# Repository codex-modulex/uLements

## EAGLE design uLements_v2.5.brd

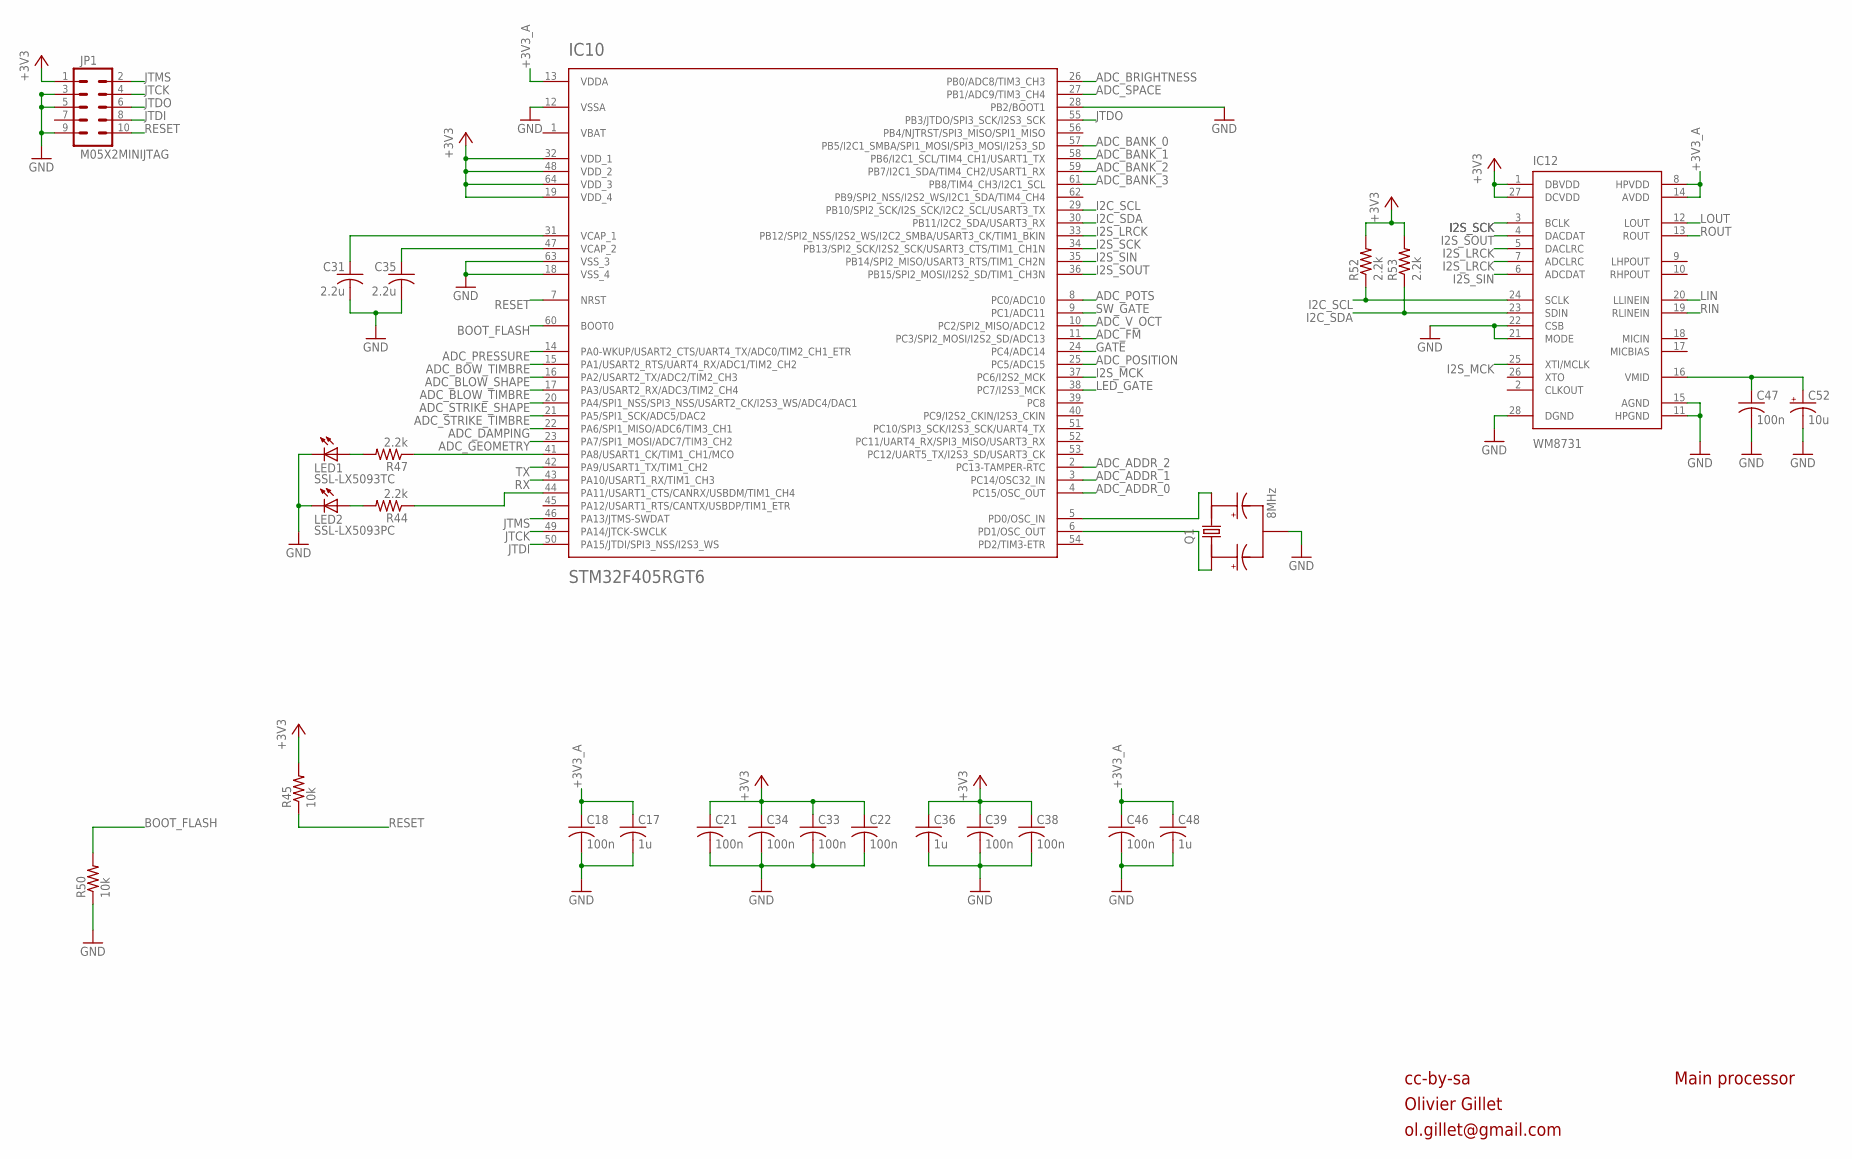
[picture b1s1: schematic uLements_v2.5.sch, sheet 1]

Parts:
C17, C36, C48: 1u; C0603
C18, C21, C22, C33, C34, C38, C39, C46, C47: 100n; C0603
C31, C35: 2.2u; C0805
C52: 10u; PANASONIC_B
IC10: STM32F405RGT6; TQFP-10X10-64
IC12: WM8731; SSOP28
JP1: M05X2MINIJTAG; 2X5-1.27
LED1: SSL-LX5093TC; LED5MM
LED2: SSL-LX5093PC; LED5MM
Q1: 8MHz; INSTRUO_CRYSTAL_SMALLER
R44, R47, R52, R53: 2.2k; R0603
R45, R50: 10k; R0603

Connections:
+3V3: C21.1, C22.1, C33.1, C34.1, C36.1, C38.1, C39.1, IC10.19 (VDD_4), IC10.32 (VDD_1), IC10.48 (VDD_2), IC10.64 (VDD_3), IC12.1 (DBVDD), IC12.27 (DCVDD), JP1.1, R45.2, R52.2, R53.2; also elsewhere on the board
+3V3_A: C17.1, C18.1, C46.1, C48.1, IC10.13 (VDDA), IC12.8 (HPVDD), IC12.14 (AVDD); also elsewhere on the board
ADC_ADDR_0: IC10.4 (PC15/OSC_OUT); also elsewhere on the board
ADC_ADDR_1: IC10.3 (PC14/OSC32_IN); also elsewhere on the board
ADC_ADDR_2: IC10.2 (PC13-TAMPER-RTC); also elsewhere on the board
ADC_BANK_0: IC10.57 (PB5/I2C1_SMBA/SPI1_MOSI/SPI3_MOSI/I2S3_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); also elsewhere on the board
ADC_BANK_1: IC10.58 (PB6/I2C1_SCL/TIM4_CH1/USART1_TX); also elsewhere on the board
ADC_BANK_2: IC10.59 (PB7/I2C1_SDA/TIM4_CH2/USART1_RX); also elsewhere on the board
ADC_BANK_3: IC10.61 (PB8/TIM4_CH3/I2C1_SCL); also elsewhere on the board
ADC_BLOW_SHAPE: IC10.16 (PA2/USART2_TX/ADC2/TIM2_CH3); also elsewhere on the board
ADC_BLOW_TIMBRE: IC10.17 (PA3/USART2_RX/ADC3/TIM2_CH4); also elsewhere on the board
ADC_BOW_TIMBRE: IC10.15 (PA1/USART2_RTS/UART4_RX/ADC1/TIM2_CH2); also elsewhere on the board
ADC_BRIGHTNESS: IC10.26 (PB0/ADC8/TIM3_CH3); also elsewhere on the board
ADC_DAMPING: IC10.22 (PA6/SPI1_MISO/ADC6/TIM3_CH1); also elsewhere on the board
ADC_FM: IC10.11 (PC3/SPI2_MOSI/I2S2_SD/ADC13); also elsewhere on the board
ADC_GEOMETRY: IC10.23 (PA7/SPI1_MOSI/ADC7/TIM3_CH2); also elsewhere on the board
ADC_POSITION: IC10.25 (PC5/ADC15); also elsewhere on the board
ADC_POTS: IC10.8 (PC0/ADC10); also elsewhere on the board
ADC_PRESSURE: IC10.14 (PA0-WKUP/USART2_CTS/UART4_TX/ADC0/TIM2_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); also elsewhere on the board
ADC_SPACE: IC10.27 (PB1/ADC9/TIM3_CH4); also elsewhere on the board
ADC_STRIKE_SHAPE: IC10.20 (PA4/SPI1_NSS/SPI3_NSS/USART2_CK/I2S3_WS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); also elsewhere on the board
ADC_STRIKE_TIMBRE: IC10.21 (PA5/SPI1_SCK/ADC5/DAC2); also elsewhere on the board
ADC_V_OCT: IC10.10 (PC2/SPI2_MISO/ADC12); also elsewhere on the board
BOOT_FLASH: IC10.60 (BOOT0), R50.2
GATE: IC10.24 (PC4/ADC14); also elsewhere on the board
GND: C17.2, C18.2, C21.2, C22.2, C31.2, C33.2, C34.2, C35.2, C36.2, C38.2, C39.2, C46.2, C47.2, C48.2, C52.-, IC10.12 (VSSA), IC10.18 (VSS_4), IC10.28 (PB2/BOOT1), IC10.63 (VSS_3), IC12.11 (HPGND), IC12.15 (AGND), IC12.21 (MODE), IC12.22 (CSB), IC12.28 (DGND), JP1.3, JP1.5, JP1.9, LED1.K (C), LED2.K (C), Q1.GND, R50.1; also elsewhere on the board
I2C_SCL: IC10.29 (PB10/SPI2_SCK/I2S_SCK/I2C2_SCL/USART3_TX), IC12.24 (SCLK), R52.1
I2C_SDA: IC10.30 (PB11/I2C2_SDA/USART3_RX), IC12.23 (SDIN), R53.1
I2S_LRCK: IC10.33 (PB12/SPI2_NSS/I2S2_WS/I2C2_SMBA/USART3_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), IC12.5 (DACLRC), IC12.7 (ADCLRC)
I2S_MCK: IC10.37 (PC6/I2S2_MCK), IC12.25 (XTI/MCLK)
I2S_SCK: IC10.34 (PB13/SPI2_SCK/I2S2_SCK/USART3_CTS/TIM1_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), IC12.3 (BCLK)
I2S_SIN: IC10.35 (PB14/SPI2_MISO/USART3_RTS/TIM1_CH2N), IC12.6 (ADCDAT)
I2S_SOUT: IC10.36 (PB15/SPI2_MOSI/I2S2_SD/TIM1_CH3N), IC12.4 (DACDAT)
JTCK: IC10.49 (PA14/JTCK-SWCLK), JP1.4
JTDI: IC10.50 (PA15/JTDI/SPI3_NSS/I2S3_WS), JP1.8
JTDO: IC10.55 (PB3/JTDO/SPI3_SCK/I2S3_SCK), JP1.6
JTMS: IC10.46 (PA13/JTMS-SWDAT), JP1.2
LED_GATE: IC10.38 (PC7/I2S3_MCK); also elsewhere on the board
LIN: IC12.20 (LLINEIN); also elsewhere on the board
LOUT: IC12.12 (LOUT); also elsewhere on the board
unnamed: IC10.5 (PD0/OSC_IN), Q1.X2
unnamed: IC10.6 (PD1/OSC_OUT), Q1.X1
unnamed: C35.1, IC10.47 (VCAP_2)
unnamed: C47.1, C52.+, IC12.16 (VMID)
unnamed: C31.1, IC10.31 (VCAP_1)
unnamed: IC10.44 (PA11/USART1_CTS/CANRX/USBDM/TIM1_CH4), R44.1
unnamed: LED2.A, R44.2
unnamed: LED1.A, R47.2
unnamed: IC10.41 (PA8/USART1_CK/TIM1_CH1/MCO), R47.1
RESET: IC10.7 (NRST), JP1.10, R45.1
RIN: IC12.19 (RLINEIN); also elsewhere on the board
ROUT: IC12.13 (ROUT); also elsewhere on the board
RX: IC10.43 (PA10/USART1_RX/TIM1_CH3)
SW_GATE: IC10.9 (PC1/ADC11); also elsewhere on the board
TX: IC10.42 (PA9/USART1_TX/TIM1_CH2)
VBAT: IC10.1 (VBAT)

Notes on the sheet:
cc-by-sa
Olivier Gillet
ol.gillet@gmail.com
Main processor

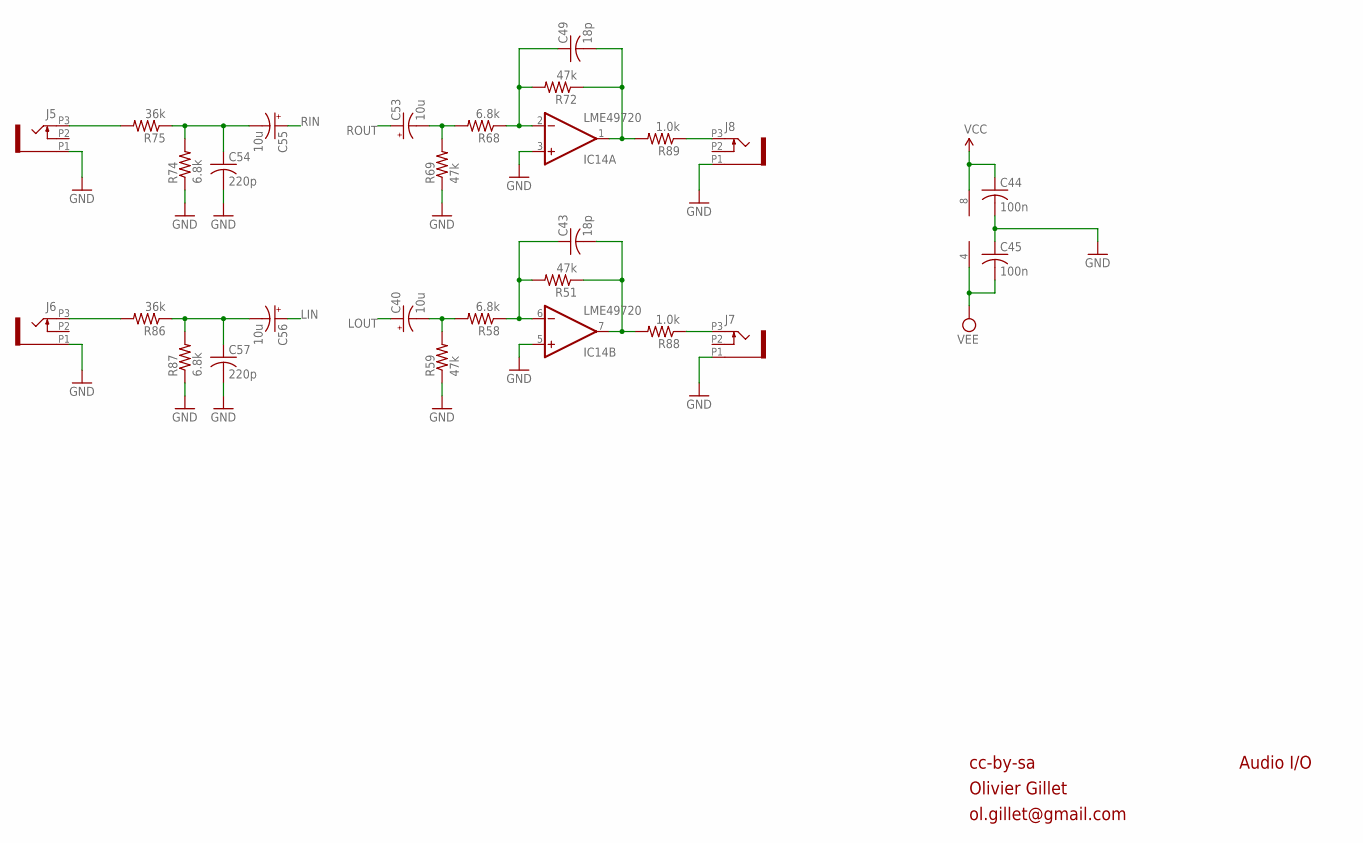
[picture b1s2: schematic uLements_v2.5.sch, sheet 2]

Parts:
C40, C53, C55, C56: 10u; PANASONIC_B
C43, C49: 18p; C0603
C44, C45: 100n; C0603
C54, C57: 220p; C0603
IC14: LME49720; SO08
J5, J6, J7, J8: PJ301_THONKICONN6; WQP_PJ_301M6
R51, R59, R69, R72: 47k; R0603
R58, R68, R74, R87: 6.8k; R0603
R75, R86: 36k; R0603
R88, R89: 1.0k; R0603

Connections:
GND: C44.2, C45.1, C54.2, C57.2, IC14.3 (+IN), IC14.5 (+IN), J5.P1 (1), J6.P1 (1), J7.P1 (1), J8.P1 (1), R59.1, R69.1, R74.1, R87.1; also elsewhere on the board
LIN: C56.+; also elsewhere on the board
LOUT: C40.+; also elsewhere on the board
LOUT_JACK: J8.P3 (3), R89.1
unnamed: C56.-, C57.1, R86.1, R87.2
unnamed: J5.P3 (3), R75.2
unnamed: J6.P3 (3), R86.2
unnamed: C54.1, C55.-, R74.2, R75.1
unnamed: C40.-, R58.2, R59.2
unnamed: C43.1, IC14.6 (-IN), R51.2, R58.1
unnamed: C43.2, IC14.7 (OUT), R51.1, R88.2
unnamed: C53.-, R68.2, R69.2
unnamed: C49.1, IC14.2 (-IN), R68.1, R72.2
unnamed: C49.2, IC14.1 (OUT), R72.1, R89.2
RIN: C55.+; also elsewhere on the board
ROUT: C53.+; also elsewhere on the board
ROUT_JACK: J7.P3 (3), R88.1
VCC: C44.1, IC14.8 (V+); also elsewhere on the board
VEE: C45.2, IC14.4 (V-); also elsewhere on the board

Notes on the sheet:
cc-by-sa
Olivier Gillet
ol.gillet@gmail.com
Audio I/O

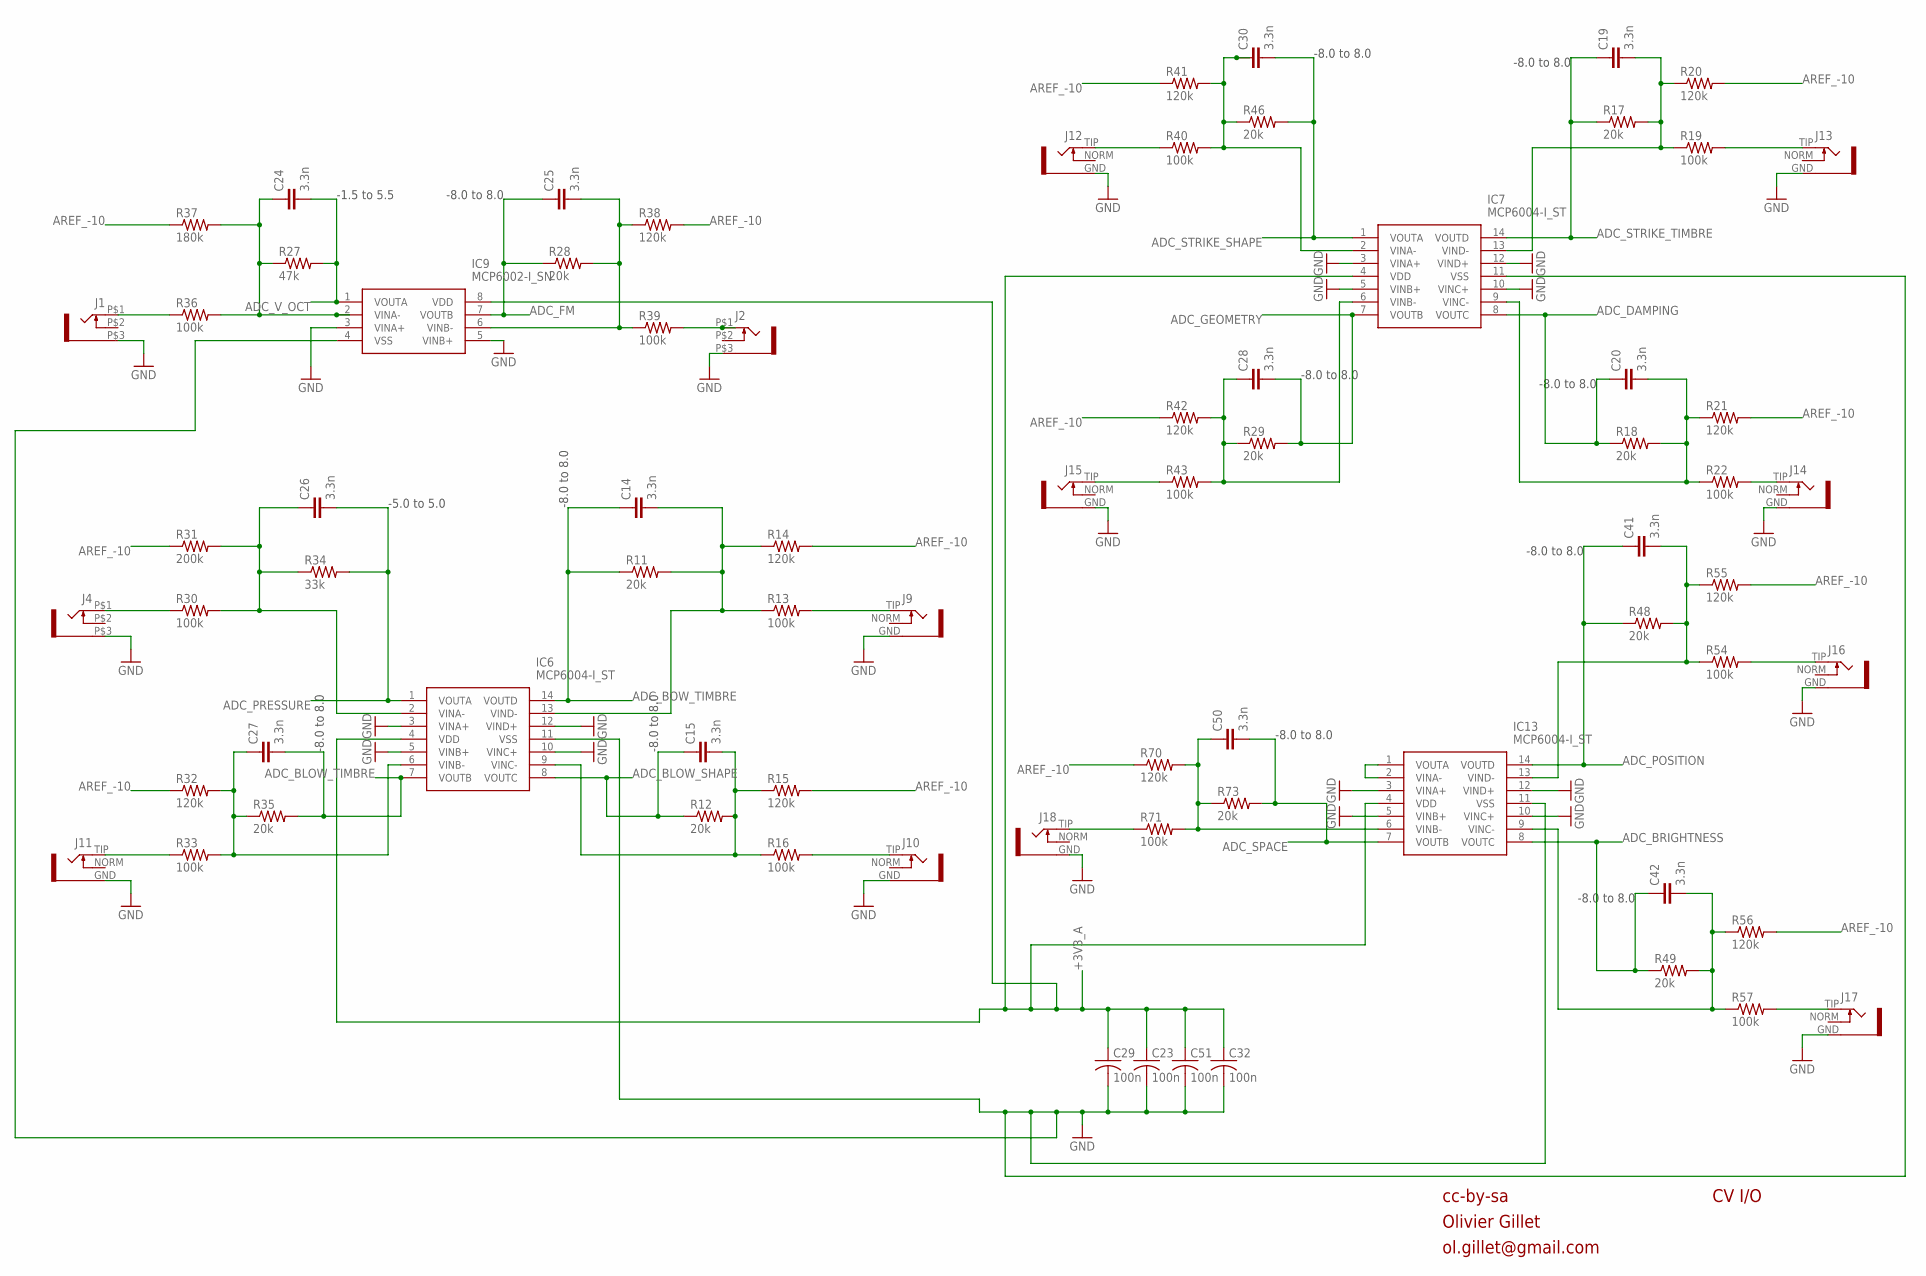
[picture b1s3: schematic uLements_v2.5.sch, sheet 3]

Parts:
C14, C15, C19, C20, C24, C25, C26, C27, C28, C30, C41, C42, C50: 3.3n; C0603
C23, C29, C32, C51: 100n; C0603
IC6, IC7, IC13: MCP6004-I_ST; SOP65P640X120-14N
IC9: MCP6002-I_SN; SOIC127P600X175-8N
J1, J2, J4: WQP-PJ301M-12_JACK
J9, J10, J11, J12, J13, J14, J15, J16, J17, J18: INSTRUO_S_JACK_S2_INV
R11, R12, R17, R18, R28, R29, R35, R46, R48, R49, R73: 20k; R0603
R13, R16, R19, R22, R30, R33, R36, R39, R40, R43, R54, R57, R71: 100k; R0603
R14, R15, R20, R21, R32, R38, R41, R42, R55, R56, R70: 120k; R0603
R27: 47k; R0603
R31: 200k; R0603
R34: 33k; R0603
R37: 180k; R0603

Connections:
+3V3_A: C23.1, C29.1, C32.1, C51.1, IC6.4 (VDD), IC7.4 (VDD), IC9.8 (VDD), IC13.4 (VDD); also elsewhere on the board
ADC_BLOW_SHAPE: C15.1, IC6.8 (VOUTC), R12.1; also elsewhere on the board
ADC_BLOW_TIMBRE: C27.2, IC6.7 (VOUTB), R35.2; also elsewhere on the board
ADC_BOW_TIMBRE: C14.1, IC6.14 (VOUTD), R11.1; also elsewhere on the board
ADC_BRIGHTNESS: C42.1, IC13.8 (VOUTC), R49.1; also elsewhere on the board
ADC_DAMPING: C20.1, IC7.8 (VOUTC), R18.1; also elsewhere on the board
ADC_FM: C25.1, IC9.7 (VOUTB), R28.1; also elsewhere on the board
ADC_GEOMETRY: C28.2, IC7.7 (VOUTB), R29.2; also elsewhere on the board
ADC_POSITION: C41.1, IC13.14 (VOUTD), R48.1; also elsewhere on the board
ADC_PRESSURE: C26.2, IC6.1 (VOUTA), R34.2; also elsewhere on the board
ADC_SPACE: C50.2, IC13.7 (VOUTB), R73.2; also elsewhere on the board
ADC_STRIKE_SHAPE: C30.2, IC7.1 (VOUTA), R46.2; also elsewhere on the board
ADC_STRIKE_TIMBRE: C19.1, IC7.14 (VOUTD), R17.1; also elsewhere on the board
ADC_V_OCT: C24.2, IC9.1 (VOUTA), R27.2; also elsewhere on the board
AREF_-10: R14.2, R15.2, R20.2, R21.2, R31.1, R32.1, R37.1, R38.2, R41.1, R42.1, R55.2, R56.2, R70.1; also elsewhere on the board
GND: C23.2, C29.2, C32.2, C51.2, IC6.3 (VINA+), IC6.5 (VINB+), IC6.10 (VINC+), IC6.11 (VSS), IC6.12 (VIND+), IC7.3 (VINA+), IC7.5 (VINB+), IC7.10 (VINC+), IC7.11 (VSS), IC7.12 (VIND+), IC9.3 (VINA+), IC9.4 (VSS), IC9.5 (VINB+), IC13.3 (VINA+), IC13.5 (VINB+), IC13.10 (VINC+), IC13.11 (VSS), IC13.12 (VIND+), J1.P$3 (1), J2.P$3 (1), J4.P$3 (1), J9.GND, J10.GND, J11.GND, J12.GND, J13.GND, J14.GND, J15.GND, J16.GND, J17.GND, J18.GND; also elsewhere on the board
unnamed: J15.TIP, R43.1
unnamed: C28.1, IC7.6 (VINB-), R29.1, R42.2, R43.2
unnamed: C20.2, IC7.9 (VINC-), R18.2, R21.1, R22.1
unnamed: J18.TIP, R71.1
unnamed: C41.2, IC13.13 (VIND-), R48.2, R54.1, R55.1
unnamed: J11.TIP, R33.1
unnamed: IC13.1 (VOUTA), IC13.2 (VINA-)
unnamed: J4.P$1 (2), R30.1
unnamed: J14.TIP, R22.2
unnamed: C50.1, IC13.6 (VINB-), R70.2, R71.2, R73.1
unnamed: C26.1, IC6.2 (VINA-), R30.2, R31.2, R34.1
unnamed: J13.TIP, R19.2
unnamed: J16.TIP, R54.2
unnamed: J17.TIP, R57.2
unnamed: C19.2, IC7.13 (VIND-), R17.2, R19.1, R20.1
unnamed: C42.2, IC13.9 (VINC-), R49.2, R56.1, R57.1
unnamed: J12.TIP, R40.1
unnamed: C25.2, IC9.6 (VINB-), R28.2, R38.1, R39.1
unnamed: C27.1, IC6.6 (VINB-), R32.2, R33.2, R35.1
unnamed: J10.TIP, R16.2
unnamed: C30.1, IC7.2 (VINA-), R40.2, R41.2, R46.1
unnamed: J1.P$1 (2), R36.1
unnamed: J2.P$1 (2), R39.2
unnamed: C24.1, IC9.2 (VINA-), R27.1, R36.2, R37.2
unnamed: J9.TIP, R13.2
unnamed: C15.2, IC6.9 (VINC-), R12.2, R15.1, R16.1
unnamed: C14.2, IC6.13 (VIND-), R11.2, R13.1, R14.1

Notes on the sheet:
cc-by-sa
Olivier Gillet
ol.gillet@gmail.com
CV I/O
-1.5 to 5.5
-8.0 to 8.0
-5.0 to 5.0

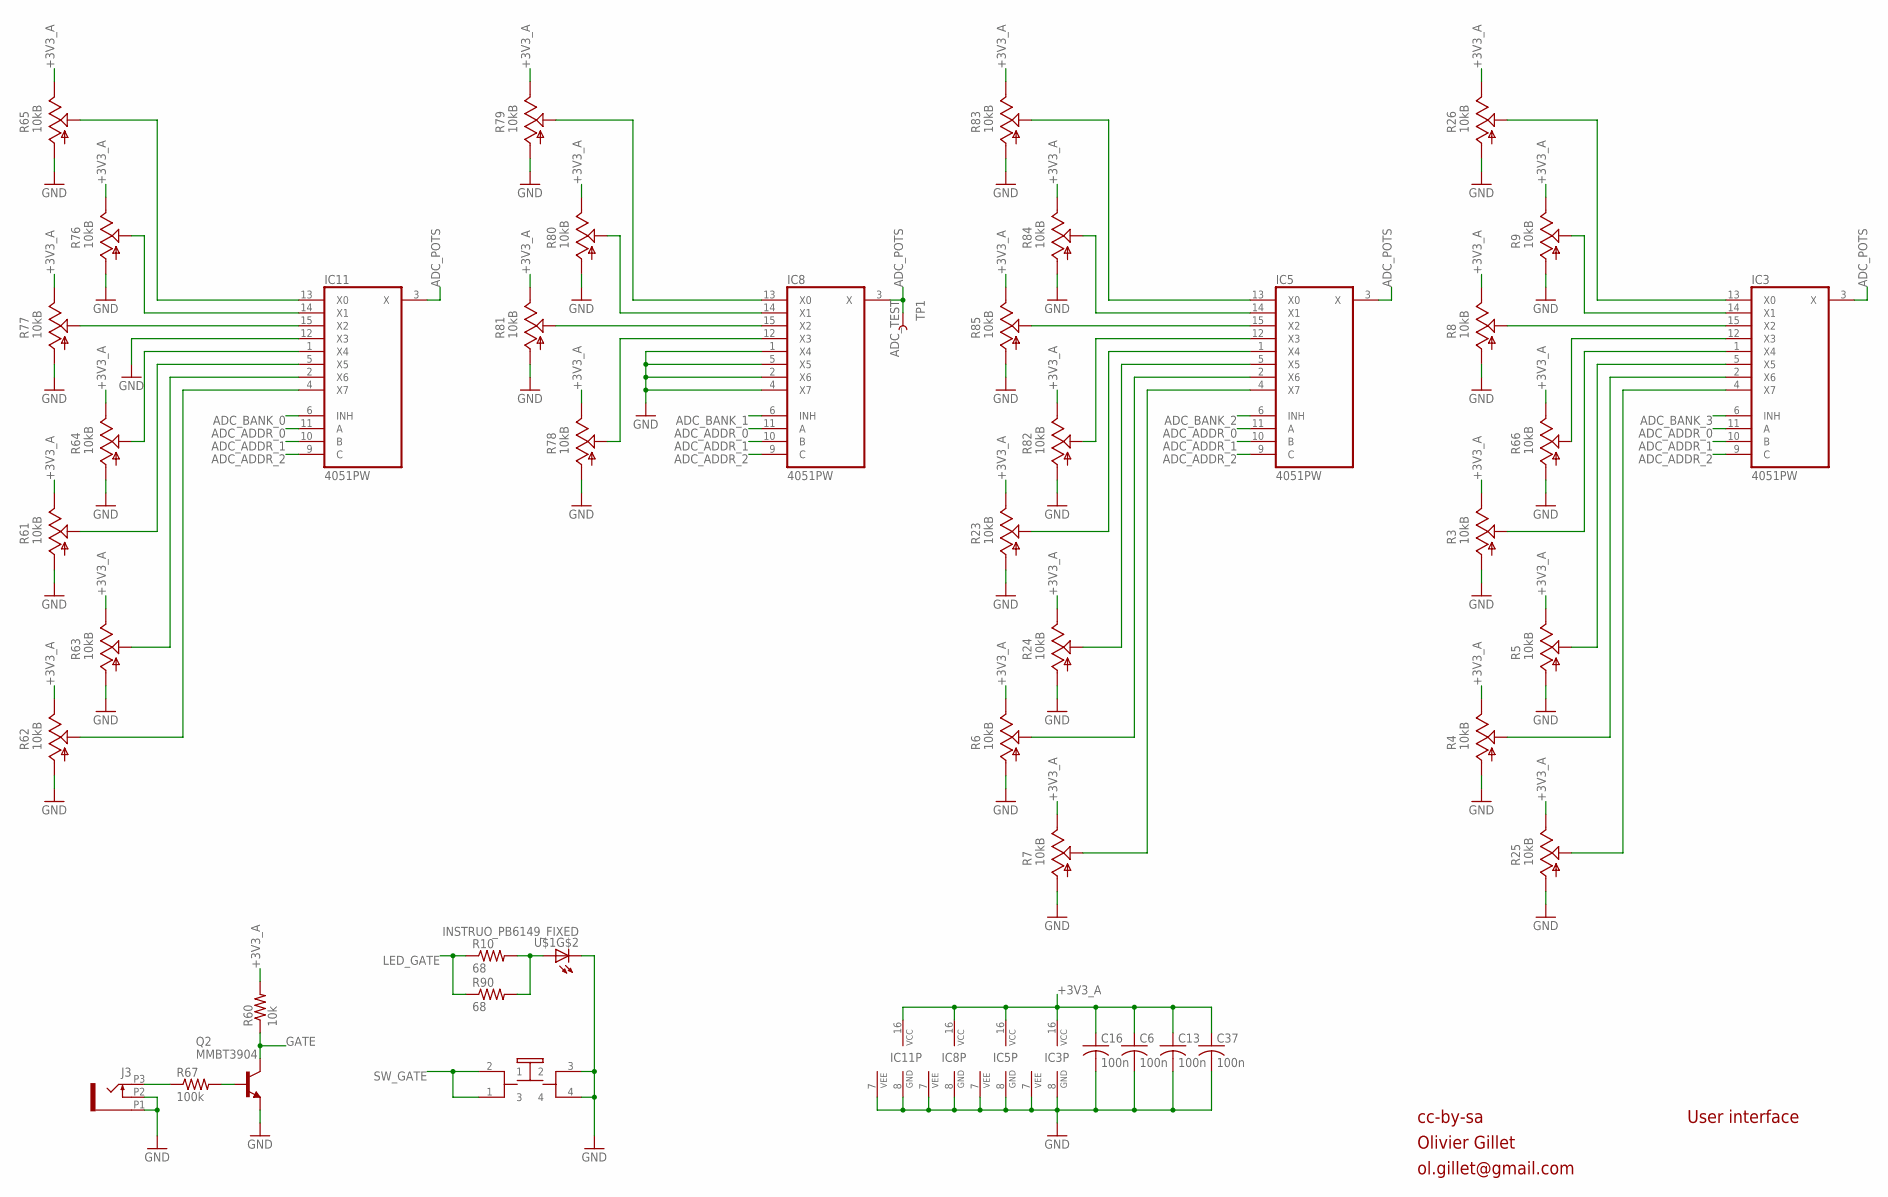
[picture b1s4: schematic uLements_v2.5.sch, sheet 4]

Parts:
C6, C13, C16, C37: 100n; C0603
IC3, IC5, IC8, IC11: 4051PW; TSSOP16
J3: PJ301_THONKICONN6; WQP_PJ_301M6
Q2: MMBT3904; SOT23-BEC
R3, R4, R5, R6, R7, R8, R9, R23, R24, R25, R26, R61, R62, R63, R64, R65, R66: 10kB; OG-POTS_ALPS_POT_VERTICAL
R10, R90: 68; R0603
R60: 10k; R0603
R67: 100k; R0603
R76, R77, R78, R79, R80, R81, R82, R83, R84, R85: 10kB; ALPS_POT_VERTICAL
TP1: ADC_TEST; PAD.03X.03
U$1: INSTRUO_PB6149_FIXED; INSTRUO_PB6149L

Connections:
+3V3_A: C6.1, C13.1, C16.1, C37.1, IC3.16 (VCC), IC5.16 (VCC), IC8.16 (VCC), IC11.16 (VCC), R3.P$1 (E), R4.P$1 (E), R5.P$1 (E), R6.P$1 (E), R7.P$1 (E), R8.P$1 (E), R9.P$1 (E), R23.P$1 (E), R24.P$1 (E), R25.P$1 (E), R26.P$1 (E), R60.2, R61.P$1 (E), R62.P$1 (E), R63.P$1 (E), R64.P$1 (E), R65.P$1 (E), R66.P$1 (E), R76.P$1 (E), R77.P$1 (E), R78.P$1 (E), R79.P$1 (E), R80.P$1 (E), R81.P$1 (E), R82.P$1 (E), R83.P$1 (E), R84.P$1 (E), R85.P$1 (E); also elsewhere on the board
ADC_ADDR_0: IC3.11 (A), IC5.11 (A), IC8.11 (A), IC11.11 (A); also elsewhere on the board
ADC_ADDR_1: IC3.10 (B), IC5.10 (B), IC8.10 (B), IC11.10 (B); also elsewhere on the board
ADC_ADDR_2: IC3.9 (C), IC5.9 (C), IC8.9 (C), IC11.9 (C); also elsewhere on the board
ADC_BANK_0: IC11.6 (INH); also elsewhere on the board
ADC_BANK_1: IC8.6 (INH); also elsewhere on the board
ADC_BANK_2: IC5.6 (INH); also elsewhere on the board
ADC_BANK_3: IC3.6 (INH); also elsewhere on the board
ADC_POTS: IC3.3 (X), IC5.3 (X), IC8.3 (X), IC11.3 (X), TP1.P$1; also elsewhere on the board
GATE: Q2.C, R60.1; also elsewhere on the board
GND: C6.2, C13.2, C16.2, C37.2, IC3.7 (VEE), IC3.8 (GND), IC5.7 (VEE), IC5.8 (GND), IC8.1 (X4), IC8.2 (X6), IC8.4 (X7), IC8.5 (X5), IC8.7 (VEE), IC8.8 (GND), IC11.7 (VEE), IC11.8 (GND), IC11.12 (X3), J3.P1 (1), J3.P2 (2), Q2.E, R3.P$3 (A), R4.P$3 (A), R5.P$3 (A), R6.P$3 (A), R7.P$3 (A), R8.P$3 (A), R9.P$3 (A), R23.P$3 (A), R24.P$3 (A), R25.P$3 (A), R26.P$3 (A), R61.P$3 (A), R62.P$3 (A), R63.P$3 (A), R64.P$3 (A), R65.P$3 (A), R66.P$3 (A), R76.P$3 (A), R77.P$3 (A), R78.P$3 (A), R79.P$3 (A), R80.P$3 (A), R81.P$3 (A), R82.P$3 (A), R83.P$3 (A), R84.P$3 (A), R85.P$3 (A), U$1.3 (2), U$1.4, U$1.K (C); also elsewhere on the board
LED_GATE: R10.1, R90.1; also elsewhere on the board
unnamed: R10.2, R90.2, U$1.A
unnamed: J3.P3 (3), R67.1
unnamed: IC11.14 (X1), R76.P$2 (S)
unnamed: IC11.13 (X0), R65.P$2 (S)
unnamed: IC11.15 (X2), R77.P$2 (S)
unnamed: IC11.1 (X4), R64.P$2 (S)
unnamed: IC11.5 (X5), R61.P$2 (S)
unnamed: IC8.14 (X1), R80.P$2 (S)
unnamed: IC8.12 (X3), R78.P$2 (S)
unnamed: IC11.2 (X6), R63.P$2 (S)
unnamed: IC11.4 (X7), R62.P$2 (S)
unnamed: IC3.12 (X3), R66.P$2 (S)
unnamed: IC8.15 (X2), R81.P$2 (S)
unnamed: IC8.13 (X0), R79.P$2 (S)
unnamed: IC3.13 (X0), R26.P$2 (S)
unnamed: IC3.15 (X2), R8.P$2 (S)
unnamed: IC5.12 (X3), R82.P$2 (S)
unnamed: Q2.B, R67.2
unnamed: IC5.4 (X7), R7.P$2 (S)
unnamed: IC3.14 (X1), R9.P$2 (S)
unnamed: IC5.2 (X6), R6.P$2 (S)
unnamed: IC5.5 (X5), R24.P$2 (S)
unnamed: IC5.1 (X4), R23.P$2 (S)
unnamed: IC3.4 (X7), R25.P$2 (S)
unnamed: IC3.2 (X6), R4.P$2 (S)
unnamed: IC3.1 (X4), R3.P$2 (S)
unnamed: IC3.5 (X5), R5.P$2 (S)
unnamed: IC5.13 (X0), R83.P$2 (S)
unnamed: IC5.14 (X1), R84.P$2 (S)
unnamed: IC5.15 (X2), R85.P$2 (S)
SW_GATE: U$1.1 (3), U$1.2 (1); also elsewhere on the board

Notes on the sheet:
cc-by-sa
Olivier Gillet
ol.gillet@gmail.com
User interface

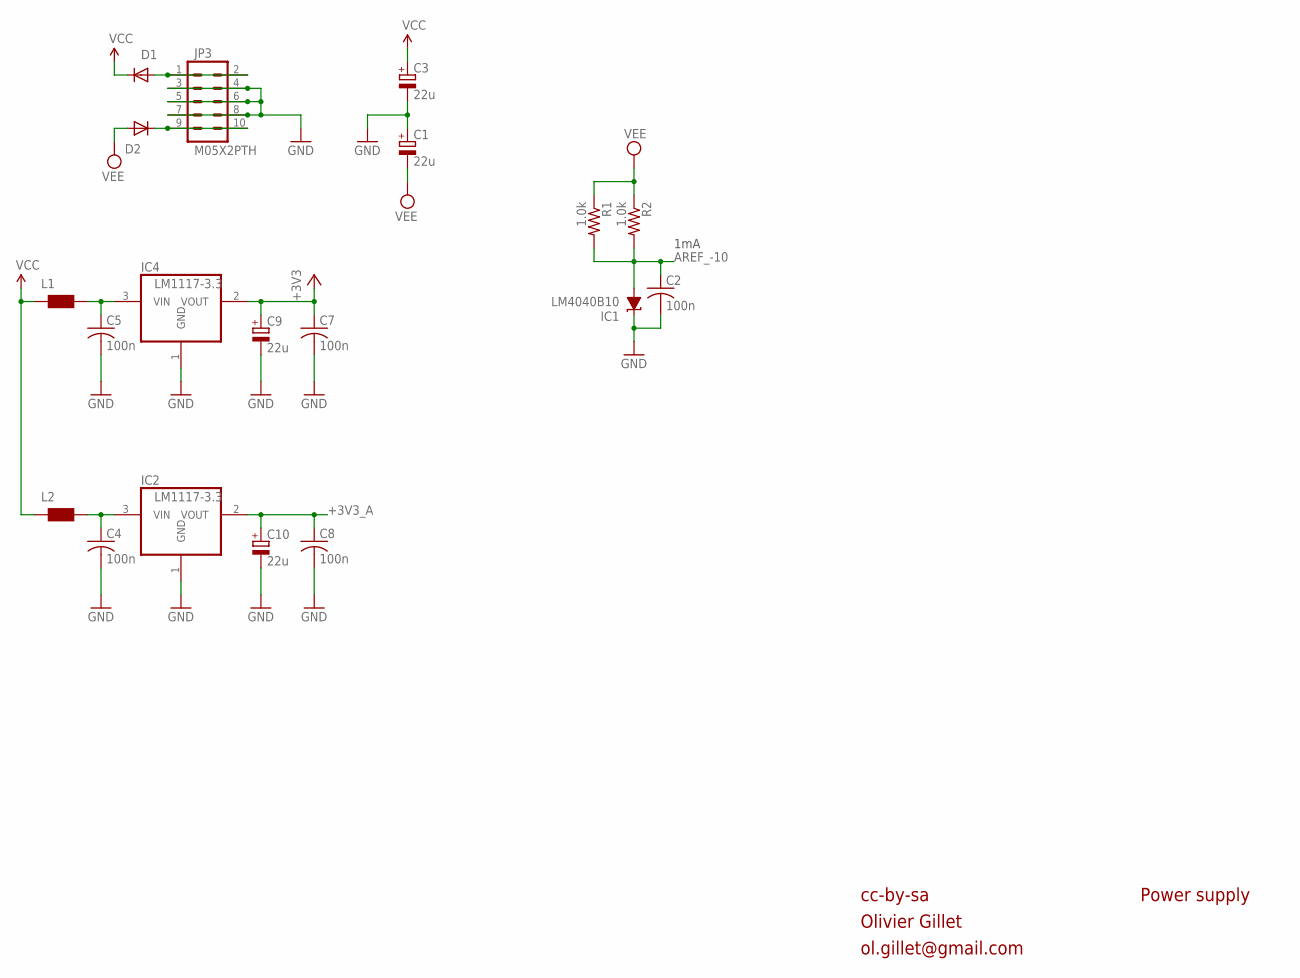
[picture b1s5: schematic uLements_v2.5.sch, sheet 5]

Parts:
C1, C3, C9, C10: 22u; PANASONIC_B
C2, C4, C5, C7, C8: 100n; C0603
D1, D2: 1N5819HW; SOD123
IC1: LM4040B10; DBZ_R-PDSO-G3
IC2, IC4: LM1117-3.3; SOT223
JP3: M05X2PTH; AVR_ICSP
L1, L2: WE-CBF_0603; 0603
R1, R2: 1.0k; R0603

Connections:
+3V3: C7.1, C9.+, IC4.2 (VOUT); also elsewhere on the board
+3V3_A: C8.1, C10.+, IC2.2 (VOUT); also elsewhere on the board
AREF_-10: C2.1, IC1.2 (A), R1.2, R2.2; also elsewhere on the board
GND: C1.+, C2.2, C3.-, C4.2, C5.2, C7.2, C8.2, C9.-, C10.-, IC1.1 (C), IC2.1 (GND), IC4.1 (GND), JP3.3, JP3.4, JP3.5, JP3.6, JP3.7, JP3.8; also elsewhere on the board
unnamed: D1.A, JP3.1, JP3.2
unnamed: C5.1, IC4.3 (VIN), L1.2
unnamed: D2.C, JP3.9, JP3.10
unnamed: C4.1, IC2.3 (VIN), L2.2
VCC: C3.+, D1.C, L1.1, L2.1; also elsewhere on the board
VEE: C1.-, D2.A, R1.1, R2.1; also elsewhere on the board

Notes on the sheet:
1mA
cc-by-sa
Olivier Gillet
ol.gillet@gmail.com
Power supply

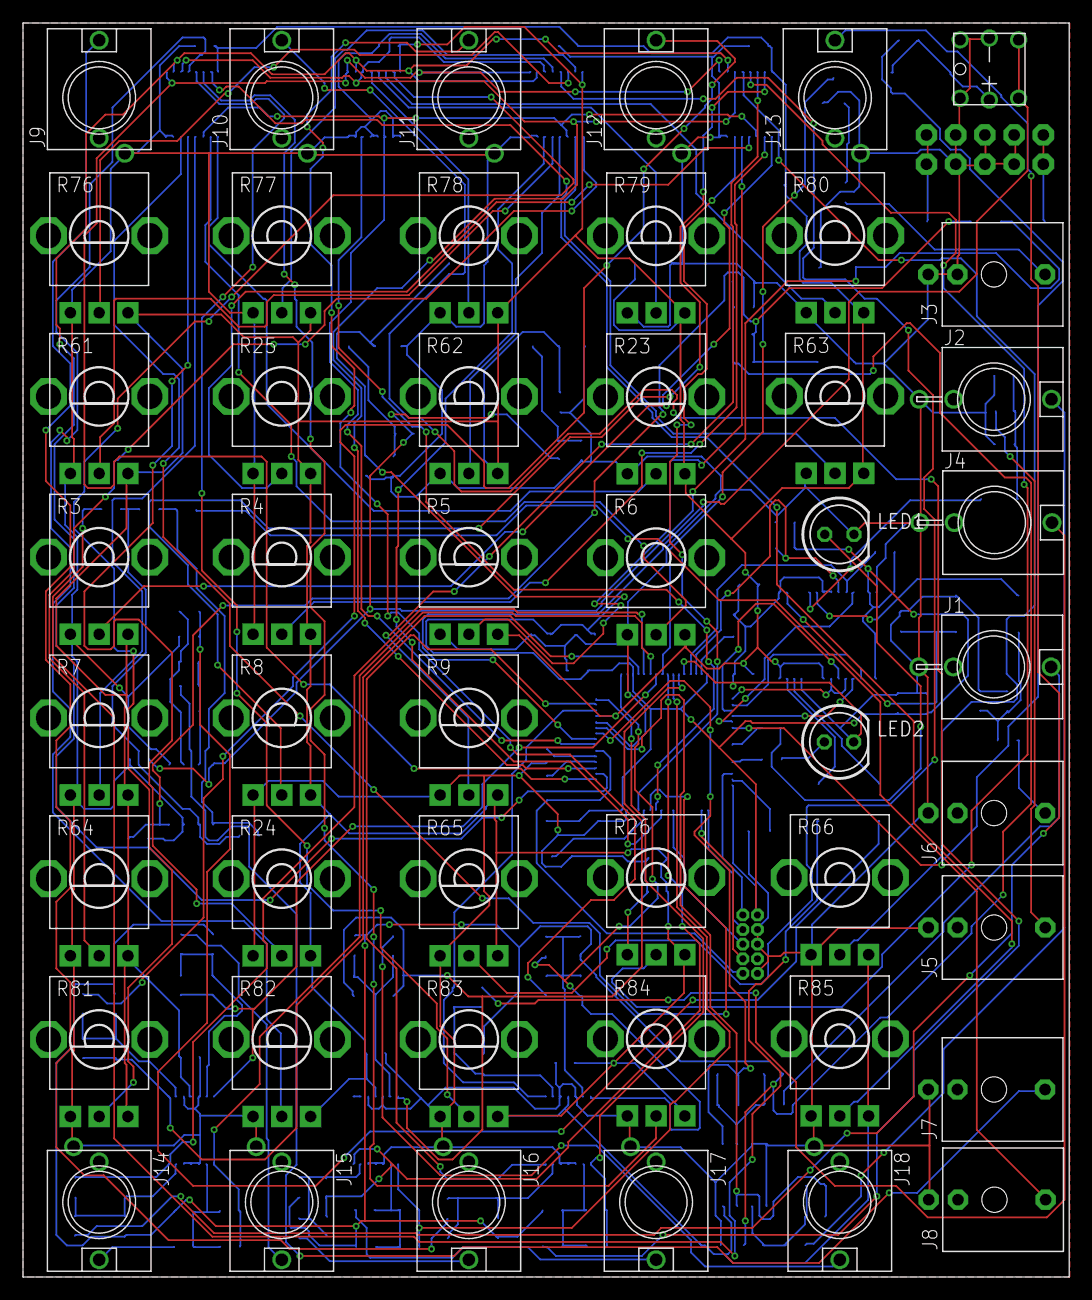
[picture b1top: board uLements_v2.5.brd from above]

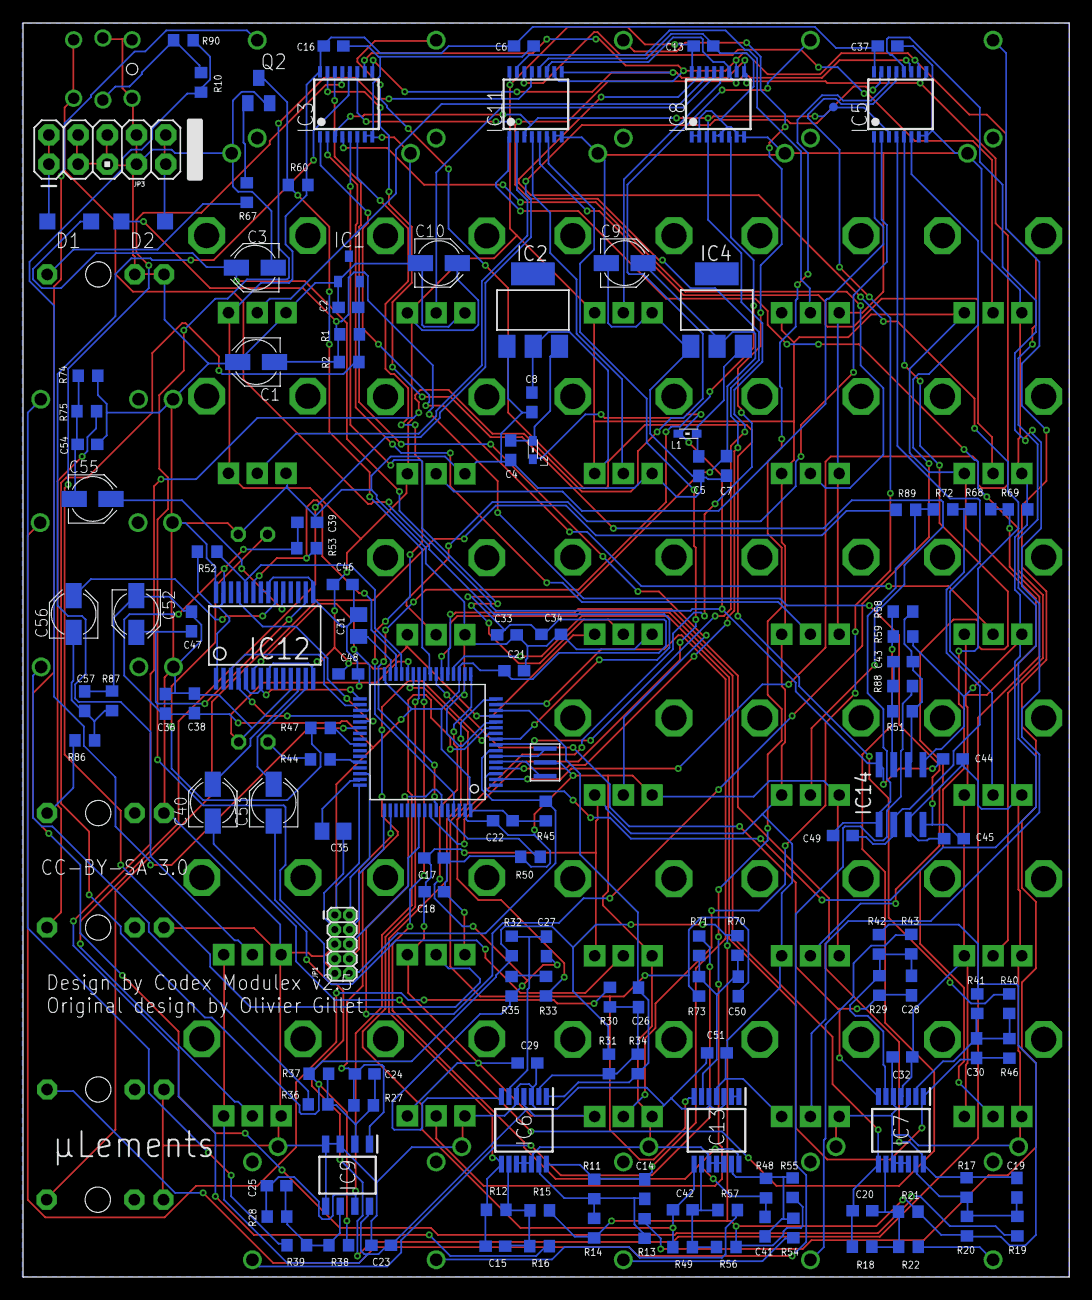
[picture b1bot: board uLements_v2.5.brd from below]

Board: 2 copper layers, 90.9 x 109.0 mm, 189 parts (141 on the bottom side), 129 nets.

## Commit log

2018-12-11 uLements files

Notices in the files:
uLements_v2.5.brd:
CC-BY-SA 3.0
